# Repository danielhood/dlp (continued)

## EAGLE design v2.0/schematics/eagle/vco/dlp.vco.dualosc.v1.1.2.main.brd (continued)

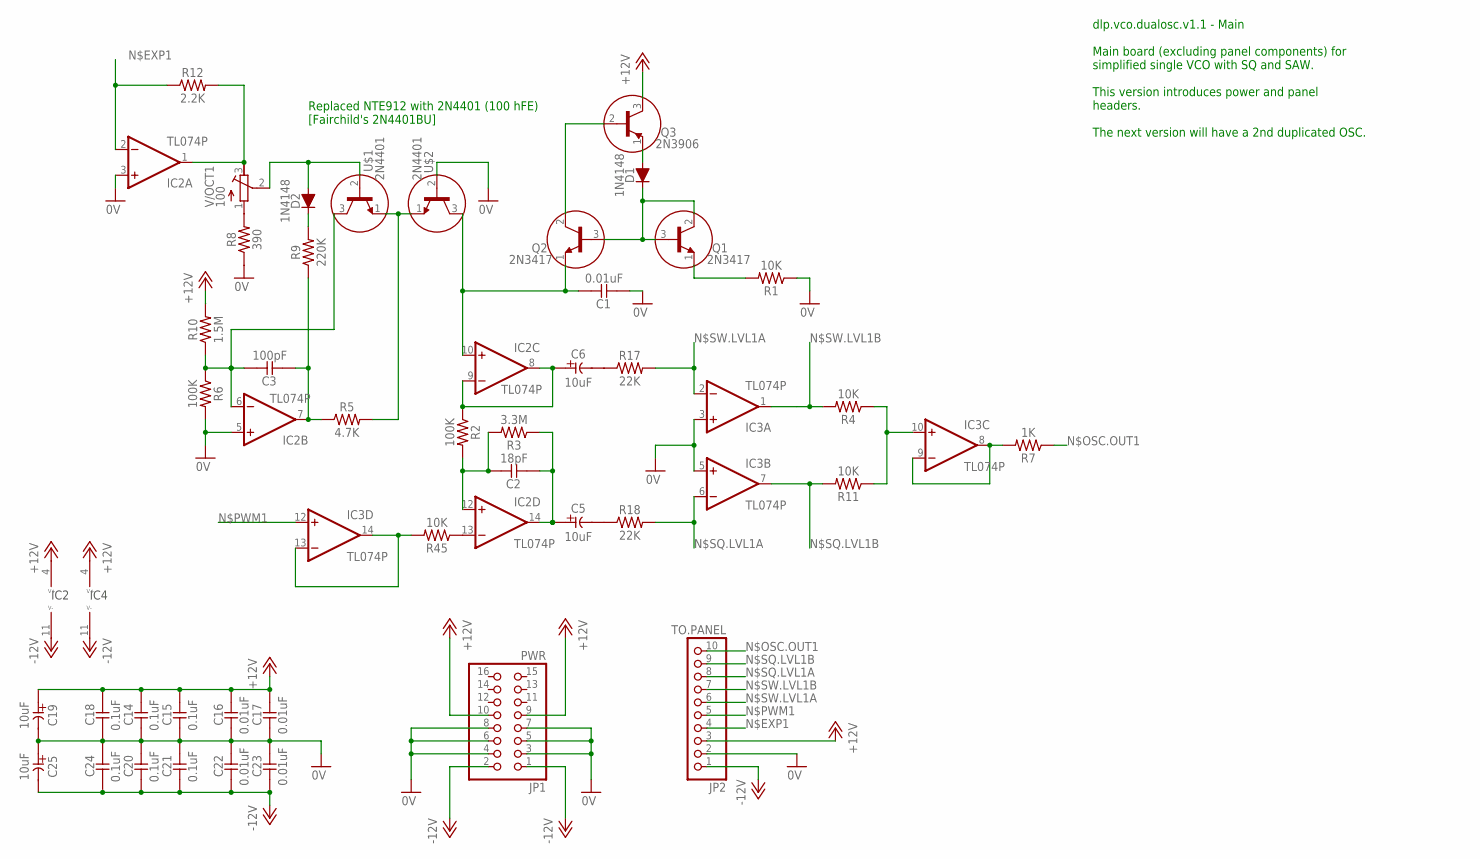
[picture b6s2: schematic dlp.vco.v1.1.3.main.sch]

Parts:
C1, C16, C17, C22, C23: 0.01uF; C025-024X044
C2: 18pF; C025-024X044
C3: 100pF; C025-024X044
C5, C6, C19, C25: 10uF; E2-5
C14, C15, C18, C20, C21, C24: 0.1uF; C025-024X044
D1, D2: 1N4148; DO35-7
IC2, IC3: TL074P; DIL14
JP1: PWR; 2X08
JP2: TO.PANEL; 1X10
Q1, Q2: 2N3417; TO92
Q3: 2N3906; TO92
R1, R4, R11, R45: 10K; 0309/10
R2, R6: 100K; 0309/10
R3: 3.3M; 0309/10
R5: 4.7K; 0309/10
R7: 1K; 0309/10
R8: 390; 0309/10
R9: 220K; 0309/10
R10: 1.5M; 0309/10
R12: 2.2K; 0309/10
R17, R18: 22K; 0309/10
U$1, U$2: 2N4401; TO92
V/OCT1: 100; RTRIM3296Y

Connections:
0V: C1.2, C14.2, C15.2, C16.2, C17.2, C18.2, C19.-, C20.1, C21.1, C22.1, C23.1, C24.1, C25.+, IC2.3 (+IN), IC2.5 (+IN), IC3.3 (+IN), IC3.5 (+IN), JP1.3, JP1.4, JP1.5, JP1.6, JP1.7, JP1.8, JP2.2, R1.1, R6.2, R8.1, U$2.2 (B); also elsewhere on the board
+12V: C14.1, C15.1, C16.1, C17.1, C18.1, C19.+, IC2.4 (V+), IC3.4 (V+), JP1.9, JP1.10, JP2.3, Q3.3 (C), R10.2
-12V: C20.2, C21.2, C22.2, C23.2, C24.2, C25.-, IC2.11 (V-), IC3.11 (V-), JP1.1, JP1.2, JP2.1
unnamed 3: C1.1, IC2.10 (+IN), Q2.1 (E), U$2.3 (C); also elsewhere on the board
unnamed: Q2.2 (C), Q3.2 (B)
unnamed: D1.A, Q3.1 (E)
unnamed: C6.+, IC2.8 (OUT), IC2.9 (-IN), R2.1
unnamed: D1.C, Q1.2 (C), Q1.3 (B), Q2.3 (B)
unnamed: Q1.1 (E), R1.2
unnamed: C2.1, IC2.12 (+IN), R2.2, R3.2
unnamed: IC2.13 (-IN), R45.1
unnamed: C2.2, C5.+, IC2.14 (OUT), R3.1
unnamed 12: D2.A, U$1.2 (B), V/OCT1.2 (S); also elsewhere on the board
unnamed 13: R5.2, U$1.1 (E), U$2.1 (E); also elsewhere on the board
unnamed: D2.C, R9.2
unnamed: R8.2, V/OCT1.1 (A)
unnamed 16: C3.1, IC2.6 (-IN), R6.1, R10.1, U$1.3 (C); also elsewhere on the board
unnamed: IC2.1 (OUT), R12.2, V/OCT1.3 (E)
unnamed: IC3.10 (+IN), R4.1, R11.1
unnamed: IC3.8 (OUT), IC3.9 (-IN), R7.2
unnamed: IC3.13 (-IN), IC3.14 (OUT), R45.2
unnamed: C6.-, R17.1
unnamed: C5.-, R18.1
N$EXP1: IC2.2 (-IN), JP2.4, R12.1
N$OSC.OUT1: JP2.10, R7.1
N$PWM1: IC3.12 (+IN), JP2.5
N$SQ.LVL1A: IC3.6 (-IN), JP2.8, R18.2
N$SQ.LVL1B: IC3.7 (OUT), JP2.9, R11.2
N$SW.LVL1A: IC3.2 (-IN), JP2.6, R17.2
N$SW.LVL1B: IC3.1 (OUT), JP2.7, R4.2

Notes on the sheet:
IC2
IC4
dlp.vco.dualosc.v1.1 - Main Main board (excluding panel components) for simplified single VCO with SQ and SAW. This version introduces power and panel headers. The next version will have a 2nd duplicated OSC.
Replaced NTE912 with 2N4401 (100 hFE) [Fairchild's 2N4401BU]

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
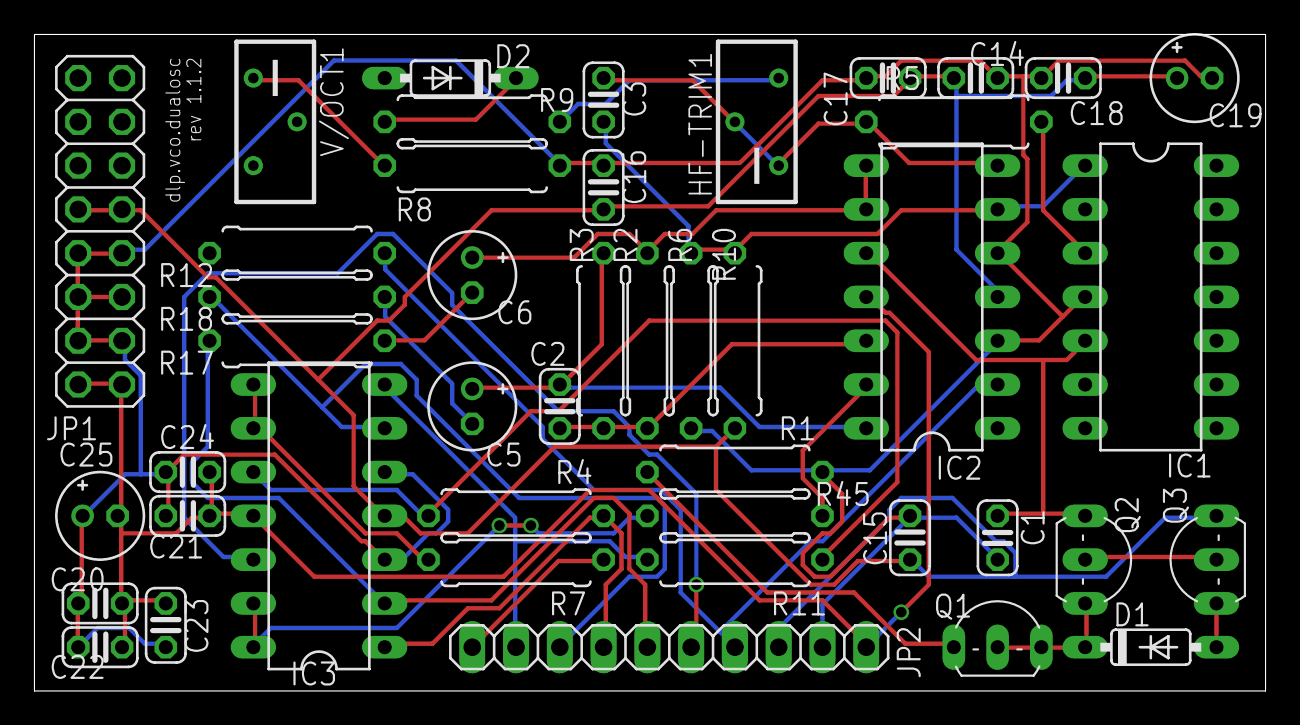
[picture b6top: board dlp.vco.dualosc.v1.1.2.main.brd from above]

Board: 2 copper layers, 71.4 x 38.1 mm, 44 parts (0 on the bottom side), 32 nets.
